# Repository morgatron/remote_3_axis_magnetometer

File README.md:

# Remote 3-Axis Magnetometer Acquisition System

A high-resolution, battery-powered remote magnetic field monitoring ecosystem supporting PNI RM3100 digital SPI magnetometers and FLC100 analog fluxgates (sampled via 24-bit TI ADS131E08 ADC).

Features universal field sensor firmware, multi-protocol receiver gateway firmware (**LoRa**, **ESP-NOW**, **BLE Coded PHY**, **WiFi UDP**), an edge relay service, a PySide6 desktop plotting app, and a central server with a real-time Web GUI dashboard.

---

## 📖 User Documentation

Complete user documentation is available in the [`docs/`](docs/) directory:

- [**Documentation Index (`docs/README.md`)**](docs/README.md)
- [**1. Getting Started Guide (`docs/1_GETTING_STARTED.md`)**](docs/1_GETTING_STARTED.md)
- [**2. Firmware & Power Optimization Guide (`docs/2_FIRMWARE_AND_POWER_GUIDE.md`)**](docs/2_FIRMWARE_AND_POWER_GUIDE.md)
- [**3. Wireless & Field Testing Guide (`docs/3_WIRELESS_AND_FIELD_TESTING.md`)**](docs/3_WIRELESS_AND_FIELD_TESTING.md)
- [**4. Central Server & Dashboards Guide (`docs/4_CENTRAL_SERVER_AND_DASHBOARDS.md`)**](docs/4_CENTRAL_SERVER_AND_DASHBOARDS.md)
- [**Active Device Profiles Reference (`IN_USE_PROFILES.md`)**](IN_USE_PROFILES.md)
- [**Minimal End-to-End Testing Setup (`TESTING_SETUP.md`)**](TESTING_SETUP.md)
- [**AI Architecture & Development Guide (`AI.md`)**](AI.md)

---

## 🚀 Quickstart

```bash
# 1. Clone & activate Conda environment
git clone https://github.com/morgatron/remote_3_axis_magnetometer.git
cd remote_3_axis_magnetometer
conda env create -f environment.yml
conda activate rm3100

# 2. Start Central Data Server
cd central_service && python server.py
# Open http://localhost:8000

# 3. Flash Heltec V4 Gateway Node
pio run -e heltec_v4_receiver -t upload --upload-port /dev/ttyACM1

# 4. Flash Heltec V4 Field Sensor Node
pio run -e heltec_v4_sensor -t upload --upload-port /dev/ttyACM0
```

---

## 🛠 Supported Hardware

| Hardware Board | Microcontroller | Radio Transceivers | Sensor Interfaces |
| :--- | :--- | :--- | :--- |
| **Heltec WiFi LoRa 32 V4** | ESP32-S3 (Dual-core LX7 @ 240 MHz) | Sub-GHz SX1262 LoRa (+22 dBm), Wi-Fi, BLE 5.0 | PNI RM3100 / ADS131E08 ADC |
| **ESP32-C6 RISC-V PCB** | ESP32-C6 (RISC-V @ 160 MHz) | Wi-Fi 6 (802.11ax), BLE 5.3 Coded PHY, 802.15.4 | PNI RM3100 / ADS131E08 ADC |
| **ESP32-C3 RISC-V PCB** | ESP32-C3 (RISC-V @ 160 MHz) | Wi-Fi 4, BLE 5.0 | PNI RM3100 / ADS131E08 ADC |

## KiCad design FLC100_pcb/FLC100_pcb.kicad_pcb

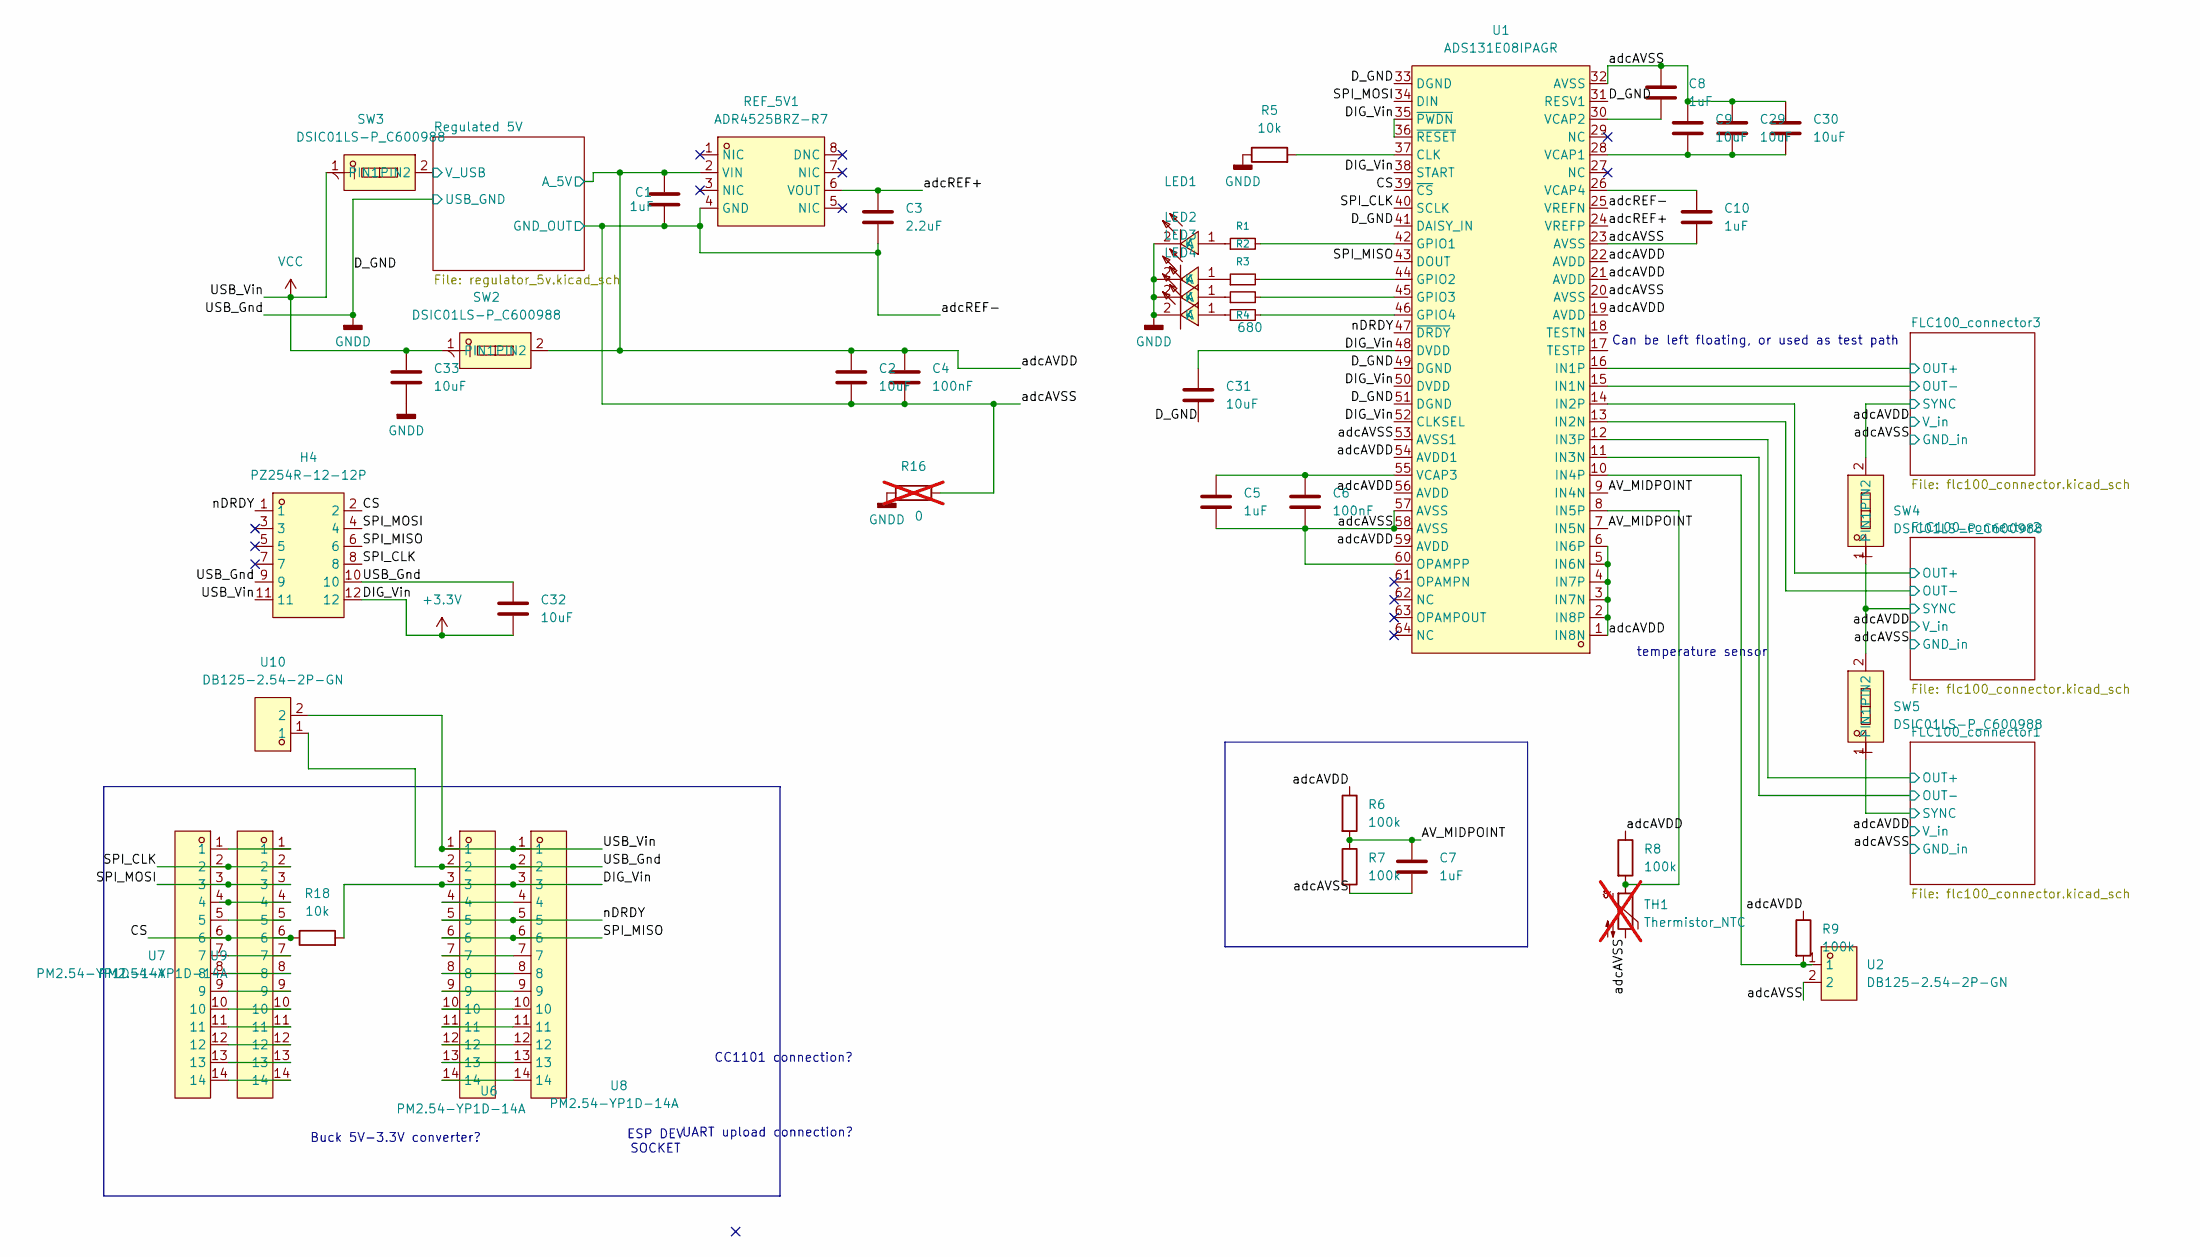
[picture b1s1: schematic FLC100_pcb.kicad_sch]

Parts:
C1, C5, C7, C8, C10: 1uF; C_0603_1608Metric
C2, C9, C29, C30, C31, C32, C33: 10uF; C_0603_1608Metric
C3: 2.2uF; C_0603_1608Metric
C4, C6: 100nF; C_0402_1005Metric
H4: PZ254R-12-12P; HDR-TH_12P-P2.54-H-M-R2-C6-S2.54; MPN PZ254R-12-12P; LCSC Part C492434
LED1, LED2, LED3, LED4: 0603White light_C2290; LED0603-R-RD_WHITE; MPN KT-0603W; LCSC Part C2290
R1, R2, R3, R4: 680; R_0603_1608Metric
R5, R18: 10k; R_0402_1005Metric
R6, R7, R8, R9: 100k; R_0805_2012Metric
R16: 0; R_0805_2012Metric; not fitted
REF_5V1: ADR4525BRZ-R7; SOIC-8_L4.9-W3.9-P1.27-LS6.0-BL; MPN ADR4525BRZ-R7; LCSC Part C403914
SW2, SW3, SW4, SW5: DSIC01LS-P_C600988; SW-SMD_2P-L3.5-W6.1-P2.54-LS9.8; MPN DSIC01LS-P; LCSC Part C600988
TH1: Thermistor_NTC; R_Axial_DIN0204_L3.6mm_D1.6mm_P2.54mm_Vertical; not fitted
U1: ADS131E08IPAGR; LQFP-64_L10.0-W10.0-P0.50-LS12.0-TL; MPN ADS131E08IPAGR; LCSC Part C190276
U2, U10: DB125-2.54-2P-GN; CONN-TH_DB125-2.54-2P-GN; MPN DB125-2.54-2P-GN-S; LCSC Part C918120
U6, U7, U8, U9: PM2.54-YP1D-14A; HDR-TH_14P-P2.54-V-F-2; MPN PM2.54-YP1D-14A; LCSC Part C22399554

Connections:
+3.3V: C31.1, C32.2, H4.12, R18.2, U1.35 (~PWDN), U1.36 (~RESET), U1.38 (START), U1.48 (DVDD), U1.50 (DVDD), U1.52 (CLKSEL), U6.3, U8.3
/AV_MIDPOINT: C7.1, R6.2, R7.1, U1.7 (IN5N), U1.9 (IN4N)
/CS: H4.2, R18.1, U1.39 (~CS), U7.6, U9.6
/FLC100_connector1/OUT+: U1.12 (IN3P); also elsewhere on the board
/FLC100_connector1/OUT-: U1.11 (IN3N); also elsewhere on the board
/FLC100_connector1/SYNC: SW5.1 (PIN1); also elsewhere on the board
/FLC100_connector2/OUT+: U1.14 (IN2P); also elsewhere on the board
/FLC100_connector2/OUT-: U1.13 (IN2N); also elsewhere on the board
/FLC100_connector2/SYNC: SW4.1 (PIN1), SW5.2 (PIN2); also elsewhere on the board
/FLC100_connector3/OUT+: U1.16 (IN1P); also elsewhere on the board
/FLC100_connector3/OUT-: U1.15 (IN1N); also elsewhere on the board
/FLC100_connector3/SYNC: SW4.2 (PIN2); also elsewhere on the board
/Regulated 5V/V_USB: SW3.2 (PIN2); also elsewhere on the board
/SPI_CLK: H4.8, U1.40 (SCLK), U7.2, U9.2
/SPI_MISO: H4.6, U1.43 (DOUT), U6.6, U8.6
/SPI_MOSI: H4.4, U1.34 (DIN), U7.3, U9.3
/adcAVDD: C1.1, C2.1, C4.1, R6.1, R8.1, R9.1, REF_5V1.2 (VIN), SW2.2 (PIN2), U1.1 (IN8N), U1.2 (IN8P), U1.3 (IN7N), U1.4 (IN7P), U1.5 (IN6N), U1.6 (IN6P), U1.19 (AVDD), U1.21 (AVDD), U1.22 (AVDD), U1.54 (AVDD1), U1.56 (AVDD), U1.59 (AVDD); also elsewhere on the board
/adcAVSS: C1.2, C2.2, C3.2, C4.2, C5.2, C6.2, C7.2, C8.1, C9.1, C10.2, C29.1, C30.1, R7.2, R16.2, REF_5V1.4 (GND), TH1.2, U1.20 (AVSS), U1.23 (AVSS), U1.25 (VREFN), U1.32 (AVSS), U1.53 (AVSS1), U1.57 (AVSS), U1.58 (AVSS), U1.60 (OPAMPP), U2.2; also elsewhere on the board
/adcREF+: C3.1, REF_5V1.6 (VOUT), U1.24 (VREFP)
/nDRDY: H4.1, U1.47 (~DRDY), U6.5, U8.5
GNDD: C31.2, C32.1, C33.2, H4.9, H4.10, LED1.2 (K), LED2.2 (K), LED3.2 (K), LED4.2 (K), R5.1, R16.1, U1.31 (RESV1), U1.33 (DGND), U1.41 (DAISY_IN), U1.49 (DGND), U1.51 (DGND), U6.2, U8.2, U10.1; also elsewhere on the board
unnamed: LED1.1 (A), R1.1
unnamed: LED2.1 (A), R2.1
unnamed: LED3.1 (A), R3.1
unnamed: LED4.1 (A), R4.1
unnamed: R5.2, U1.37 (CLK)
unnamed: R1.2, U1.42 (GPIO1)
unnamed: R2.2, U1.44 (GPIO2)
unnamed: R3.2, U1.45 (GPIO3)
unnamed: R4.2, U1.46 (GPIO4)
unnamed: R9.2, U1.10 (IN4P), U2.1
unnamed: R8.2, TH1.1, U1.8 (IN5P)
unnamed: C9.2, C29.2, C30.2, U1.28 (VCAP1)
unnamed: C8.2, U1.30 (VCAP2)
unnamed: C5.1, C6.1, U1.55 (VCAP3)
unnamed: C10.1, U1.26 (VCAP4)
unnamed: U6.4, U8.4
unnamed: U6.7, U8.7
unnamed: U6.8, U8.8
unnamed: U6.9, U8.9
unnamed: U6.10, U8.10
unnamed: U6.11, U8.11
unnamed: U6.12, U8.12
unnamed: U6.13, U8.13
unnamed: U6.14, U8.14
unnamed: U7.1, U9.1
unnamed: U7.4, U9.4
unnamed: U7.5, U9.5
unnamed: U7.7, U9.7
unnamed: U7.8, U9.8
unnamed: U7.9, U9.9
unnamed: U7.10, U9.10
unnamed: U7.11, U9.11
unnamed: U7.12, U9.12
unnamed: U7.13, U9.13
unnamed: U7.14, U9.14
VCC: C33.1, H4.11, SW2.1 (PIN1), SW3.1 (PIN1), U6.1, U8.1, U10.2

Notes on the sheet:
Can be left floating, or used as test path
CC1101 connection?
ESP DEV SOCKET
Buck 5V-3.3V converter?
temperature sensor
UART upload connection?

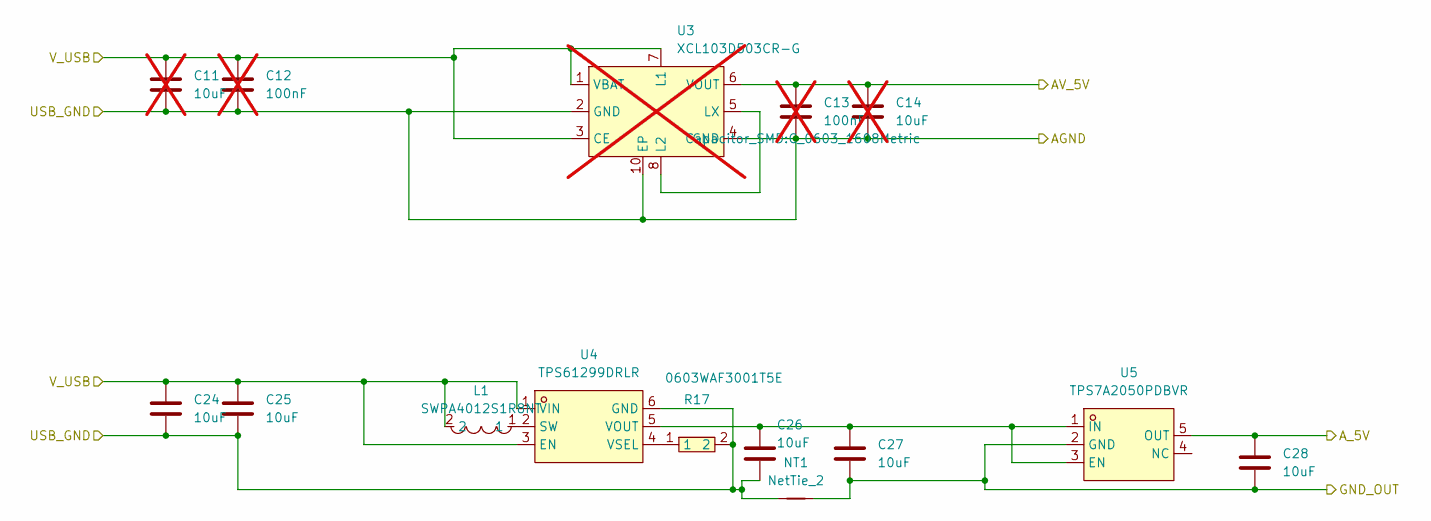
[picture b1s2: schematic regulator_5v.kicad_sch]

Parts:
C11, C14: 10uF; C_0603_1608Metric; not fitted
C12, C13: 100nF; C_0603_1608Metric; not fitted
C24, C25, C26, C27, C28: 10uF; C_0603_1608Metric
L1: SWPA4012S1R8NT; IND-SMD_L4.0-W4.0; MPN SWPA4012S1R8NT; LCSC Part C96867
NT1: NetTie_2; NetTie-2_SMD_Pad2.0mm
R17: 0603WAF3001T5E; R0603; MPN 0603WAF3001T5E; LCSC Part C4211
U3: XCL103D503CR-G; CL-2025-02_8P-L2.5-W2.0-P0.55_XCL210C331GR-G; MPN XCL103D503CR-G; LCSC Part C5439677; not fitted
U4: TPS61299DRLR; SOT-563-6_L1.6-W1.2-P0.50-LS1.6-BL; MPN TPS61299DRLR; LCSC Part C41689719
U5: TPS7A2050PDBVR; SOT-23-5_L2.9-W1.6-P0.95-LS2.8-BR; MPN TPS7A2050PDBVR; LCSC Part C2864504

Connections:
/Regulated 5V/V_USB: C11.1, C12.1, C24.1, C25.1, L1.2, U3.1 (VBAT), U3.3 (CE), U3.7 (L1), U4.1 (VIN), U4.3 (EN); also elsewhere on the board
/adcAVDD: C28.1, U5.5 (OUT); also elsewhere on the board
/adcAVSS: C27.2, C28.2, NT1.1, U5.2 (GND); also elsewhere on the board
GNDD: C11.2, C12.2, C13.2, C14.2, C24.2, C25.2, C26.2, NT1.2, R17.2, U3.2 (GND), U3.4 (GND), U3.10 (EP), U4.6 (GND); also elsewhere on the board
unnamed: C13.1, C14.1, U3.6 (VOUT)
unnamed: U3.5 (LX), U3.8 (L2)
unnamed: L1.1, U4.2 (SW)
unnamed: C26.1, C27.1, U4.5 (VOUT), U5.1 (IN), U5.3 (EN)
unnamed: R17.1, U4.4 (VSEL)

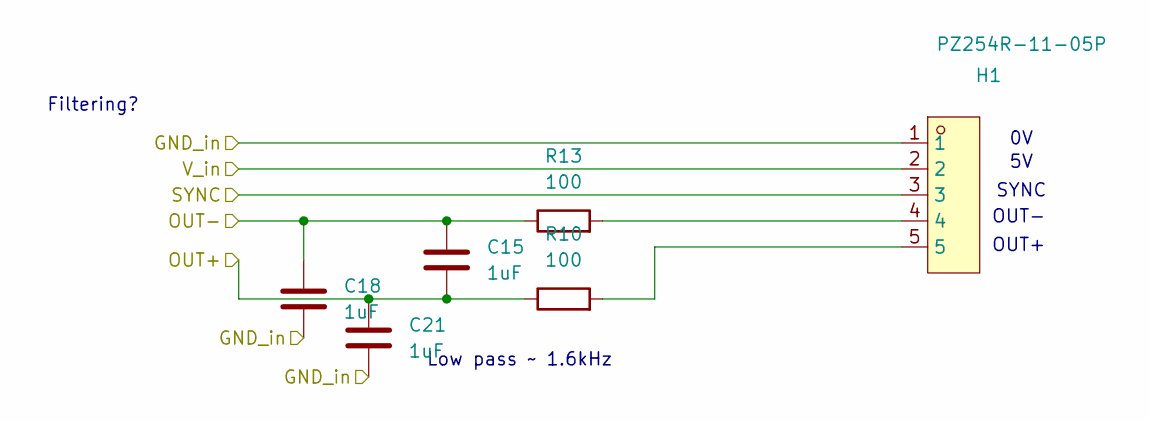
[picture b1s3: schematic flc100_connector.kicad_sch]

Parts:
C15, C18, C21: 1uF; C_0603_1608Metric
H1: PZ254R-11-05P; HDR-TH_5P-P2.54-H-M-W10.4; MPN PZ254R-11-05P; LCSC Part C492413
R10, R13: 100; R_0805_2012Metric

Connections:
/FLC100_connector1/OUT+: C15.2, C21.1, R10.1; also elsewhere on the board
/FLC100_connector1/OUT-: C15.1, C18.1, R13.1; also elsewhere on the board
/FLC100_connector1/SYNC: H1.3; also elsewhere on the board
/adcAVDD: H1.2; also elsewhere on the board
/adcAVSS: C18.2, C21.2, H1.1; also elsewhere on the board
unnamed: H1.4, R13.2
unnamed: H1.5, R10.2

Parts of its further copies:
C16, C17, C19, C20, C22, C23: 1uF; C_0603_1608Metric
H2, H3: PZ254R-11-05P; HDR-TH_5P-P2.54-H-M-W10.4; MPN PZ254R-11-05P; LCSC Part C492413
R11, R12, R14, R15: 100; R_0805_2012Metric

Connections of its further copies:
/FLC100_connector2/OUT+: C17.2, C23.1, R12.1; also elsewhere on the board
/FLC100_connector2/OUT-: C17.1, C20.1, R15.1; also elsewhere on the board
/FLC100_connector2/SYNC: H3.3; also elsewhere on the board
/FLC100_connector3/OUT+: C16.2, C22.1, R11.1; also elsewhere on the board
/FLC100_connector3/OUT-: C16.1, C19.1, R14.1; also elsewhere on the board
/FLC100_connector3/SYNC: H2.3; also elsewhere on the board
/adcAVDD: H2.2, H3.2; also elsewhere on the board
/adcAVSS: C19.2, C20.2, C22.2, C23.2, H2.1, H3.1; also elsewhere on the board
unnamed: H2.4, R14.2
unnamed: H2.5, R11.2
unnamed: H3.4, R15.2
unnamed: H3.5, R12.2

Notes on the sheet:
OUT-
Low pass ~ 1.6kHz
SYNC
OUT+
Filtering?

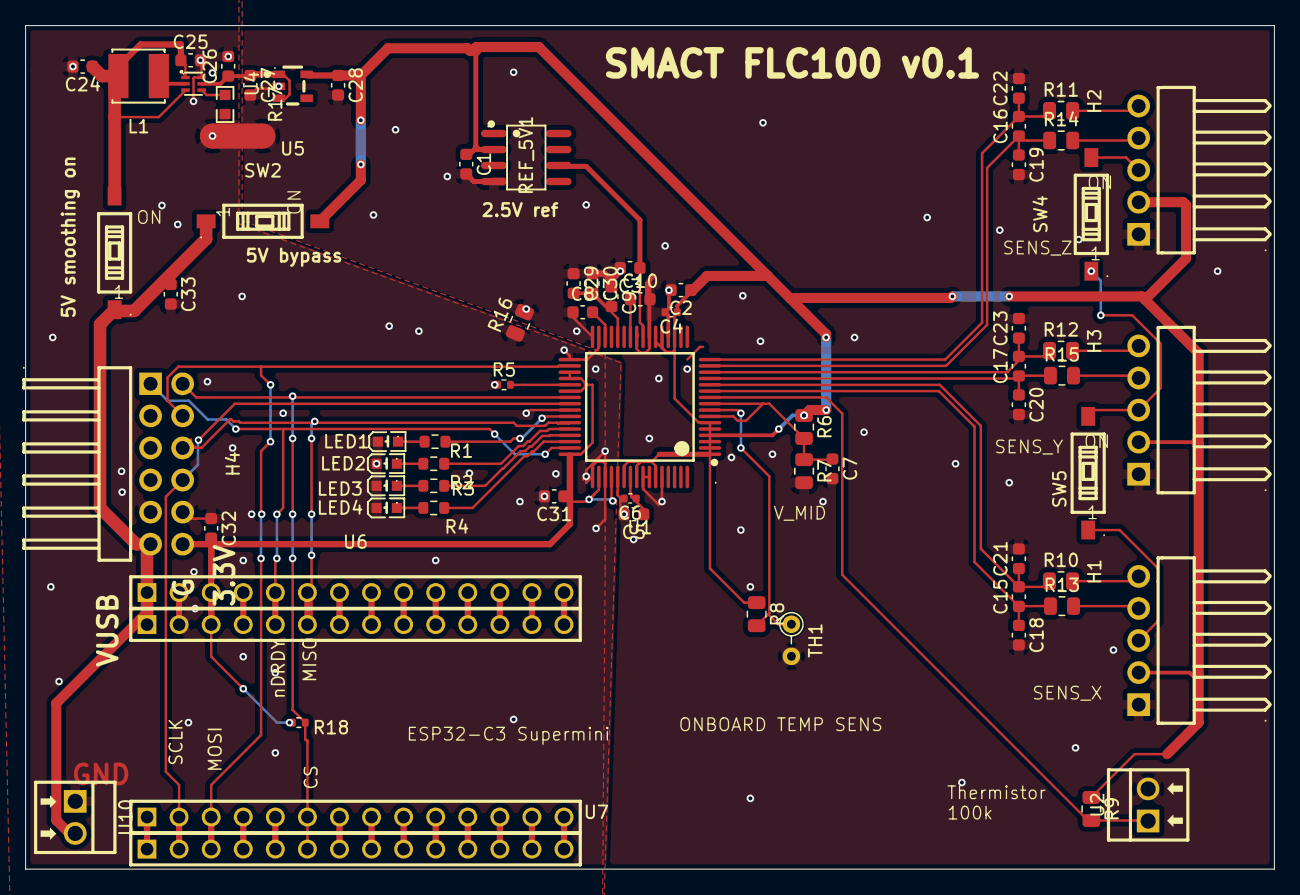
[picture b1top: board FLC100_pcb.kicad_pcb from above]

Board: 2 copper layers, 98.9 x 66.8 mm, 72 parts (0 on the bottom side), 66 nets.

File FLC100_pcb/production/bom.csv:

Designator,Footprint,Quantity,Value,LCSC Part #
"C1, C10, C15, C16, C17, C18, C19, C20, C21, C22, C23, C5, C7, C8",0603,14,1uF,
"C2, C24, C25, C26, C27, C28, C29, C30, C31, C32, C33, C9",0603,12,10uF,
C3,0603,1,2.2uF,
"C4, C6",0402,2,100nF,
"H1, H2, H3",HDR-TH_5P-P2.54-H-M-W10.4,3,PZ254R-11-05P,C492413
H4,HDR-TH_12P-P2.54-H-M-R2-C6-S2.54,1,PZ254R-12-12P,C492434
L1,IND-SMD_L4.0-W4.0,1,SWPA4012S1R8NT,C96867
"LED1, LED2, LED3, LED4",LED0603-R-RD_WHITE,4,0603White light_C2290,C2290
"R1, R2, R3, R4",0603,4,680,
"R10, R11, R12, R13, R14, R15",0805,6,100,
R17,R0603,1,0603WAF3001T5E,C4211
"R18, R5",0402,2,10k,
"R6, R7, R8, R9",0805,4,100k,
REF_5V1,SOIC-8_L4.9-W3.9-P1.27-LS6.0-BL,1,ADR4525BRZ-R7,C403914
"SW2, SW3, SW4, SW5",SW-SMD_2P-L3.5-W6.1-P2.54-LS9.8,4,DSIC01LS-P_C600988,C600988
U1,LQFP-64_L10.0-W10.0-P0.50-LS12.0-TL,1,ADS131E08IPAGR,C190276
"U10, U2",CONN-TH_DB125-2.54-2P-GN,2,DB125-2.54-2P-GN,C918120
U4,SOT-563-6_L1.6-W1.2-P0.50-LS1.6-BL,1,TPS61299DRLR,C41689719
U5,SOT-23-5_L2.9-W1.6-P0.95-LS2.8-BR,1,TPS7A2050PDBVR,C2864504
"U6, U7, U8, U9",HDR-TH_14P-P2.54-V-F-2,4,PM2.54-YP1D-14A,C22399554

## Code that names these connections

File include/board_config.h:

#ifndef BOARD_CONFIG_H
#define BOARD_CONFIG_H

#include <Arduino.h>

#if defined(HELTEC_V4) || defined(ARDUINO_heltec_wifi_lora_32_V3)
// Heltec WiFi LoRa 32 V3 / V4 (ESP32-S3 + SX1262)
#define BOARD_NAME   "Heltec WiFi LoRa 32 V4 (ESP32-S3)"
#define BOARD_HAS_LORA 1
#ifndef LORA_TX_POWER_DBM
#define LORA_TX_POWER_DBM 0 // 0 dBm SX1262 drive level + ~20 dB FEM PA gain = ~+20 dBm total radiated EIRP
#endif
#define SCK_PIN      41
#define MOSI_PIN     42
#define MISO_PIN     40
#define DRDY_PIN     38
#define CS_PIN       39
#define LED_PIN      35
#define LED_ON       HIGH
#define LED_OFF      LOW
#define VEXT_PIN     36

// LoRa Radio Pins for Heltec V4
#define LORA_CS_PIN   8
#define LORA_DIO1_PIN 14
#define LORA_RST_PIN  12
#define LORA_BUSY_PIN 13
#define LORA_SCK_PIN  9
#define LORA_MOSI_PIN 10
#define LORA_MISO_PIN 11

// Heltec V4 Front-End Module (FEM: GC1109 / KCT8103L) Control Pins
#define LORA_FEM_PWR_PIN  7   // VFEM_Ctrl (Active-HIGH: enables 3.3V power via TLV75733 LDO)
#define LORA_FEM_CSD_PIN  2   // PA_CSD (Active-HIGH: enables FEM LNA/PA out of shutdown)
#define LORA_FEM_CPS_PIN  46  // PA_CPS (Power select: High = +30dBm PA mode, Low = Bypass)
#define LORA_FEM_CTX_PIN  5   // PA_CTX (V4.3 KCT8103L: LOW = RX LNA mode, HIGH = TX mode)

#elif defined(XIAO_S3_WIO_SX1262) || defined(ARDUINO_XIAO_ESP32S3)
// Seeed Studio XIAO ESP32-S3 + Wio-SX1262 Mezzanine Board
#define BOARD_NAME   "Seeed Studio XIAO ESP32-S3 + Wio-SX1262"
#define BOARD_HAS_LORA 1
#ifndef LORA_TX_POWER_DBM
#define LORA_TX_POWER_DBM 2 // +2 dBm for bench testing to avoid saturating Heltec V4 LNA at <1m
#endif

// Sensor SPI Pins (XIAO D8=SCK, D9=MISO, D10=MOSI)
#define SCK_PIN      7
#define MOSI_PIN     9
#define MISO_PIN     8
#define CS_PIN       4   // D3 (GPIO4)
#define DRDY_PIN     3   // D2 (GPIO3)
#define LED_PIN      21  // User LED on XIAO ESP32-S3 (Active-LOW)
#define LED_ON       LOW
#define LED_OFF      HIGH
#define VBAT_ADC_PIN 1   // GPIO1 (D0 / A0) for Battery ADC
#define VBAT_DIVIDER_RATIO 2.0f

// LoRa Radio Pins for Seeed Wio-SX1262 (40-pin B2B mezzanine connector)
#define LORA_CS_PIN        41
#define LORA_DIO1_PIN      39
#define LORA_RST_PIN       42
#define LORA_BUSY_PIN      40
#define LORA_RF_SWITCH_PIN 38
#define LORA_SCK_PIN       7
#define LORA_MISO_PIN      8
#define LORA_MOSI_PIN      9
#define LORA_TCXO_VOLTAGE  1.8f

#elif defined(CONFIG_IDF_TARGET_ESP32C6) || defined(ARDUINO_ARCH_ESP32C6)
// Seeed Studio XIAO ESP32-C6 Pinout (in Supermini carrier socket)
#define BOARD_NAME   "Seeed Studio XIAO ESP32-C6"
#define SCK_PIN      1   // SCLK
#define MOSI_PIN     2   // MOSI
#define CS_PIN       23  // CS
#define MISO_PIN     19  // MISO
#define DRDY_PIN     20  // nDRDY
#define LED_PIN      15  // Yellow User LED on XIAO ESP32-C6 (Active-LOW)
#define LED_ON       LOW
#define LED_OFF      HIGH
#define VBAT_ADC_PIN 0   // GPIO0 (ADC1_CH0) for Battery Voltage Divider
#define VBAT_DIVIDER_RATIO 2.0f // Factor of 2 voltage divider

#elif defined(CONFIG_IDF_TARGET_ESP32C3) || defined(ARDUINO_ARCH_ESP32C3)
// ESP32-C3 Supermini Pinout
#define BOARD_NAME   "ESP32-C3 Supermini"
#define SCK_PIN      6
#define MOSI_PIN     7
#define MISO_PIN     2
#define DRDY_PIN     3
#define CS_PIN       10
#define LED_PIN      8   // Blue User LED on ESP32-C3 Supermini (Active-LOW)
#define LED_ON       LOW
#define LED_OFF      HIGH
#define VBAT_ADC_PIN 4   // GPIO4 (ADC1_CH4) for Battery Voltage Divider
#define VBAT_DIVIDER_RATIO 2.0f // Factor of 2 voltage divider

#else
// Legacy ESP32 Dev Module Pinout [DEPRECATED]
#define BOARD_NAME   "Legacy ESP32 Dev Module (WROOM)"
#define SCK_PIN      18
#define MISO_PIN     19
#define MOSI_PIN     23
#define CS_PIN       5
#define DRDY_PIN     4
#define LED_PIN      2
#define LED_ON       HIGH
#define LED_OFF      LOW
#endif

#define RESET_PIN   -1

#if defined(HELTEC_V4) || defined(ARDUINO_heltec_wifi_lora_32_V3)
// Battery Measurement Pins for Heltec WiFi LoRa 32 V3 / V4 (ESP32-S3)
#define VBAT_ADC_PIN   1
#define VBAT_CTRL_PIN  37
#define VBAT_DIVIDER_RATIO 4.90f // 390k / 100k divider + P-FET drop compensation (4.90x)
#endif

// Global battery cache
extern float g_cachedBatteryVoltage;

/**
 * @brief Measures real battery voltage via ADC and updates global cache.
 *        Should be called during the 10-second radio burst wake window.
 */
inline float sampleBatteryVoltage(bool force = false) {
    static uint32_t lastSampleMs = 0;
    uint32_t now = millis();

    // Only perform physical ADC conversion once every 60 seconds (~every 6 batches)
    if (!force && lastSampleMs > 0 && (now - lastSampleMs < 60000)) {
        return (g_cachedBatteryVoltage > 0.0f) ? g_cachedBatteryVoltage : 0.0f;
    }
    lastSampleMs = now;

#if defined(VBAT_ADC_PIN) && defined(VBAT_CTRL_PIN)
    pinMode(VBAT_CTRL_PIN, OUTPUT);
    digitalWrite(VBAT_CTRL_PIN, LOW); // Active-LOW gate on Heltec V3/V4 P-MOSFET
    delay(5);                          // 5ms required for 390k/100k RC filter capacitor to charge

    int raw = analogRead(VBAT_ADC_PIN);
    uint32_t rawMv = analogReadMilliVolts(VBAT_ADC_PIN);

    // Polarity fallback: if reading is ~0, check if this PCB revision uses active-HIGH control
    if (raw < 50) {
        digitalWrite(VBAT_CTRL_PIN, HIGH);
        delay(5);
        int rawHigh = analogRead(VBAT_ADC_PIN);
        if (rawHigh > raw) {
            raw = rawHigh;
            rawMv = analogReadMilliVolts(VBAT_ADC_PIN);
        }
    }

    pinMode(VBAT_CTRL_PIN, INPUT); // Disconnect divider to eliminate quiescent sleep drain

    if (raw > 50) {
        // eFuse factory-calibrated millivolt scaling with 4.90x divider factor
        float measured = (float)rawMv * (VBAT_DIVIDER_RATIO / 1000.0f);
        // Fallback for non-calibrated eFuse: standard 12-bit ADC scaling (raw / 238.7)
        if (measured < 2.0f && raw > 50) {
            measured = (float)raw / 238.7f;
        }

        if (g_cachedBatteryVoltage <= 0.0f) {
            g_cachedBatteryVoltage = measured;
        } else {
            g_cachedBatteryVoltage = 0.75f * g_cachedBatteryVoltage + 0.25f * measured; // Low-pass filter
        }
    }

    return (g_cachedBatteryVoltage > 0.0f) ? g_cachedBatteryVoltage : 0.0f;
#elif defined(VBAT_ADC_PIN)
    pinMode(VBAT_ADC_PIN, INPUT);
    analogSetPinAttenuation(VBAT_ADC_PIN, ADC_11db);

    // 4-sample averaging to smooth out ADC noise
    uint32_t sumMv = 0;
    for (int i = 0; i < 4; i++) {
        sumMv += analogReadMilliVolts(VBAT_ADC_PIN);
        delayMicroseconds(50);
    }
    uint32_t rawMv = sumMv / 4;

    #ifndef VBAT_DIVIDER_RATIO
    #define VBAT_DIVIDER_RATIO 2.0f
    #endif

    float measured = (float)rawMv * (VBAT_DIVIDER_RATIO / 1000.0f);

    if (g_cachedBatteryVoltage <= 0.0f) {
        g_cachedBatteryVoltage = measured;
    } else {
        g_cachedBatteryVoltage = 0.75f * g_cachedBatteryVoltage + 0.25f * measured; // Low-pass filter
    }

    return g_cachedBatteryVoltage;
#else
    g_cachedBatteryVoltage = 3.70f;
    return 3.70f;
#endif
}

/**
 * @brief Returns the cached battery voltage instantly (0ms latency, zero ADC/sleep overhead).
 */
inline float getBatteryVoltage() {
    return (g_cachedBatteryVoltage > 0.0f) ? g_cachedBatteryVoltage : 3.70f;
}

inline uint16_t sampleBatteryMilliVolts(bool force = false) {
    float v = sampleBatteryVoltage(force);
    return (uint16_t)(v * 1000.0f);
}

inline uint16_t getBatteryMilliVolts() {
    return (uint16_t)(getBatteryVoltage() * 1000.0f);
}

// Backward-compatible aliases
inline float readBatteryVoltage() { return getBatteryVoltage(); }
inline uint16_t readBatteryMilliVolts() { return getBatteryMilliVolts(); }

#ifndef LORA_TX_POWER_DBM
#define LORA_TX_POWER_DBM 22
#endif

inline void initBoardPower() {
#ifdef VEXT_PIN
    pinMode(VEXT_PIN, OUTPUT);
    digitalWrite(VEXT_PIN, LOW); // Pull Vext LOW to enable external power rail on Heltec V3/V4
    delay(50);
#endif
#ifdef VBAT_CTRL_PIN
    pinMode(VBAT_CTRL_PIN, INPUT); // Default to High-Z / off
#endif
}

#endif // BOARD_CONFIG_H

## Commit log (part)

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2026-05-08 Initial commit. No wifi yet
2026-05-26 latest
2026-06-02 it runs!
2026-06-16 fix: sample rate selection for rm3100s
2026-06-30 added FLC100 PCB
